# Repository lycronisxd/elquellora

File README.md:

<h3 align="center">
<picture>
  <source media="(prefers-color-scheme: dark)" srcset="images/elquellora_title_white.png">
  <source media="(prefers-color-scheme: light)" srcset="images/elquellora_title_black.png">
  
</picture><br \>
<picture>
  <source media="(prefers-color-scheme: dark)" srcset="images/author_white.png">
  <source media="(prefers-color-scheme: light)" srcset="images/author_black.png">
  
</picture>
<br \>
a lil hackpad based off the design of ulquiorra from bleach!<br \>
designed for stardance, hack club.<br \>
<br \>
<div align="center">

</div>
<hr>
<h3 align="left">get started.</h3>
<h4 align="left">
<a href="instructions.md">click here</a> to go to the instructions on how to get started!
</h4>
<hr>
<h3 align="left">about the board.</h3>
<h4 align="left">
el que llora is a 4 key hackpad with pcb art made by me,<br \>
designed with inspiration and quotes from<br \>
ulquiorra cifer from bleach!<br \>
<br \>
i wanted to make a project based off of bleach for a while<br \>
(you can probably tell by my other project <a href="https://github.com/lycronisxd/peroxide">peroxide</a>)<br \>
but finally thought of a design that would look cool in practice, so here we are!
</h4>

<hr>

<h3 align="left">features of the board.</h3>
<h4 align="left">
<ul>
<li>xiao rp2040 based</li>
<li>0.91 inch oled display</li>
<li>4x mechanical keys</li>
<li>2x ec11 rotary encoders</li>
<li>6x sk6812mini-e leds (not per-key rgb though)</li>
<li>custom bleach-inspired pcb art</li>
<li>bare-pcb design</li>
</ul>
</h4>

<hr>

<h3 align="left">design images.</h3>
<h4 align="center">
<br \>
<br \>
<br \>
<br \>
<br \>
<br \>

</h4>

<hr>

<h3 align="left">bill of materials.</h3>

|item no.|part no.|part name                 |qty.|supplier    |unit cost|total cost|notes                                            |
|--------|--------|--------------------------|----|------------|---------|----------|-------------------------------------------------|
|1       |PCB-001 |elquellora pcb            |5   |jlcpcb      | $0.40   | $7.19    |$2 for 5 pcbs + $5.12 for shipping               |
|2       |PCB-002 |seeed studio xiao rp2040  |1   |hack club   |N/A      |N/A       |provided in hackpad kit                          |
|3       |PCB-003 |1n4148 diodes             |4   |hack club   |N/A      |N/A       |provided in hackpad kit                          |
|4       |PCB-004 |0.91 inch oled            |1   |hack club   |N/A      |N/A       |provided in hackpad kit                          |
|5       |PCB-005 |ec11 rotary encoders      |2   |hack club   |N/A      |N/A       |provided in hackpad kit                          |
|6       |PCB-006 |sk6812 mini-e leds        |6   |hack club   |N/A      |N/A       |provided in hackpad kit                          |
|7       |PCB-007 |mx style switches         |4   |hack club   |N/A      |N/A       |provided in hackpad kit                          |
|8       |3D-001  |m3x5mmx4mm heatset inserts|4   |hack club   |N/A      |N/A       |provided in hackpad kit                          |
|9       |3D-002  |m3x16mm screws            |4   |hack club   |N/A      |N/A       |provided in hackpad kit                          |
|10      |3D-003  |3d printed case           |1   |print legion|?        |?         |will update when receiving a quote from a printer|
|11      |3D-004  |3d printed encoder knobs  |2   |print legion|?        |?         |will update when receiving a quote from a printer|

<hr>

<h3 align="left">my other stuff.</h3>
<h4 align="left">
a custom rp2040 dev board, <a href="https://github.com/lycronisxd/peroxide">peroxide</a><br \>
<br \>
an 18 key, per key rgb macropad with an oled screen, <a href="https://github.com/lycronisxd/pentoxide">pentoxide</a><br \>
<br \>
a custom sim-racing shifter, <a href="https://github.com/lycronisxd/a-shift">a-shift</a><br \>
<br \>
a custome corexy 3d printer, <a href="https://github.com/lycronisxd/https://github.com/lycronisxd/polylactic">polylactic</a><br \>
<br \>
a handwired split mechanical keyboard, <a href="https://github.com/lycronisxd/e-split">e-split</a>
</h4>

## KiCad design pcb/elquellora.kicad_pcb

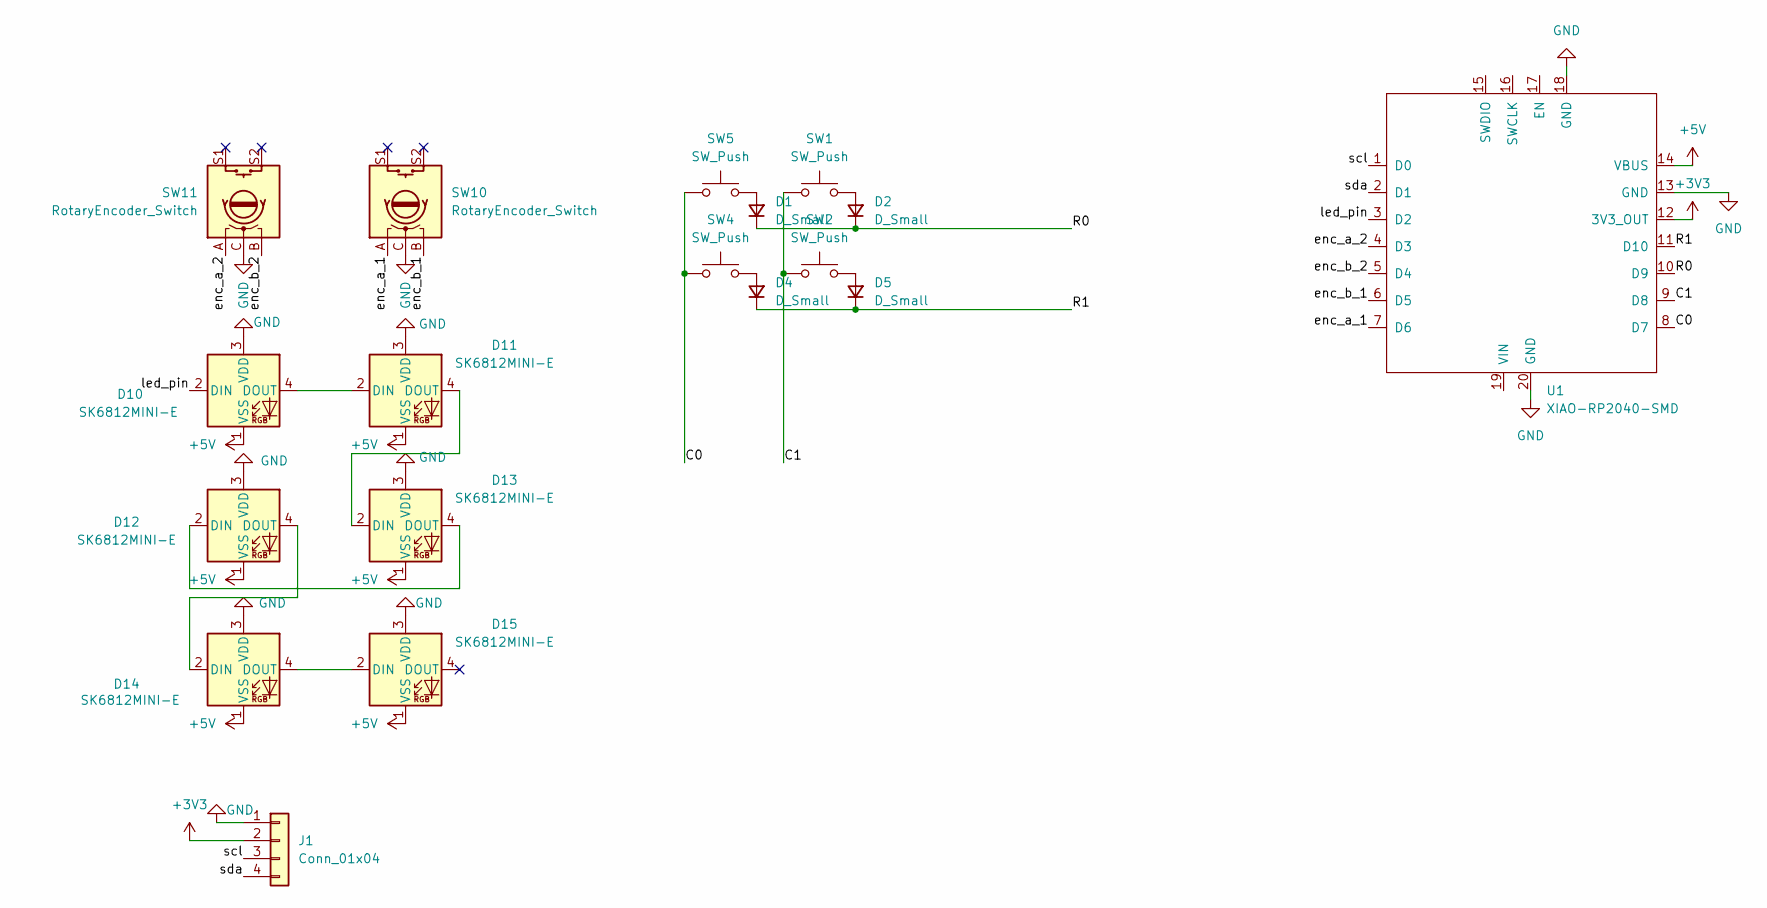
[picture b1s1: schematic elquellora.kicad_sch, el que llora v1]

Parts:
D1, D2, D4, D5: D_Small; Diode_DO-35
D10, D11, D12, D13, D14, D15: SK6812MINI-E; SK6812MINI-E_fixed
J1: Conn_01x04; PinHeader_1x04_P2.54mm_Vertical
SW1, SW2, SW4, SW5: SW_Push; SW_Cherry_MX_1.00u_PCB
SW10, SW11: RotaryEncoder_Switch; RotaryEncoder_Alps_EC11E-Switch_Vertical_H20mm
U1: XIAO-RP2040-SMD

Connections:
+3V3: J1.2, U1.12 (3V3_OUT)
+5V: D10.1 (VSS), D11.1 (VSS), D12.1 (VSS), D13.1 (VSS), D14.1 (VSS), D15.1 (VSS), U1.14 (VBUS)
/C0: SW4.1, SW5.1, U1.8 (D7)
/C1: SW1.1, SW2.1, U1.9 (D8)
/R0: D1.1 (K), D2.1 (K), U1.10 (D9)
/R1: D4.1 (K), D5.1 (K), U1.11 (D10)
/enc_a_1: SW10.A, U1.7 (D6)
/enc_a_2: SW11.A, U1.4 (D3)
/enc_b_1: SW10.B, U1.6 (D5)
/enc_b_2: SW11.B, U1.5 (D4)
/led_pin: D10.2 (DIN), U1.3 (D2)
/scl: J1.3, U1.1 (D0)
/sda: J1.4, U1.2 (D1)
GND: D10.3 (VDD), D11.3 (VDD), D12.3 (VDD), D13.3 (VDD), D14.3 (VDD), D15.3 (VDD), J1.1, SW10.C, SW11.C, U1.13 (GND), U1.18 (GND), U1.20 (GND)
unnamed: D1.2 (A), SW5.2
unnamed: D2.2 (A), SW1.2
unnamed: D4.2 (A), SW4.2
unnamed: D5.2 (A), SW2.2
unnamed: D10.4 (DOUT), D11.2 (DIN)
unnamed: D11.4 (DOUT), D13.2 (DIN)
unnamed: D12.2 (DIN), D13.4 (DOUT)
unnamed: D12.4 (DOUT), D14.2 (DIN)
unnamed: D14.4 (DOUT), D15.2 (DIN)

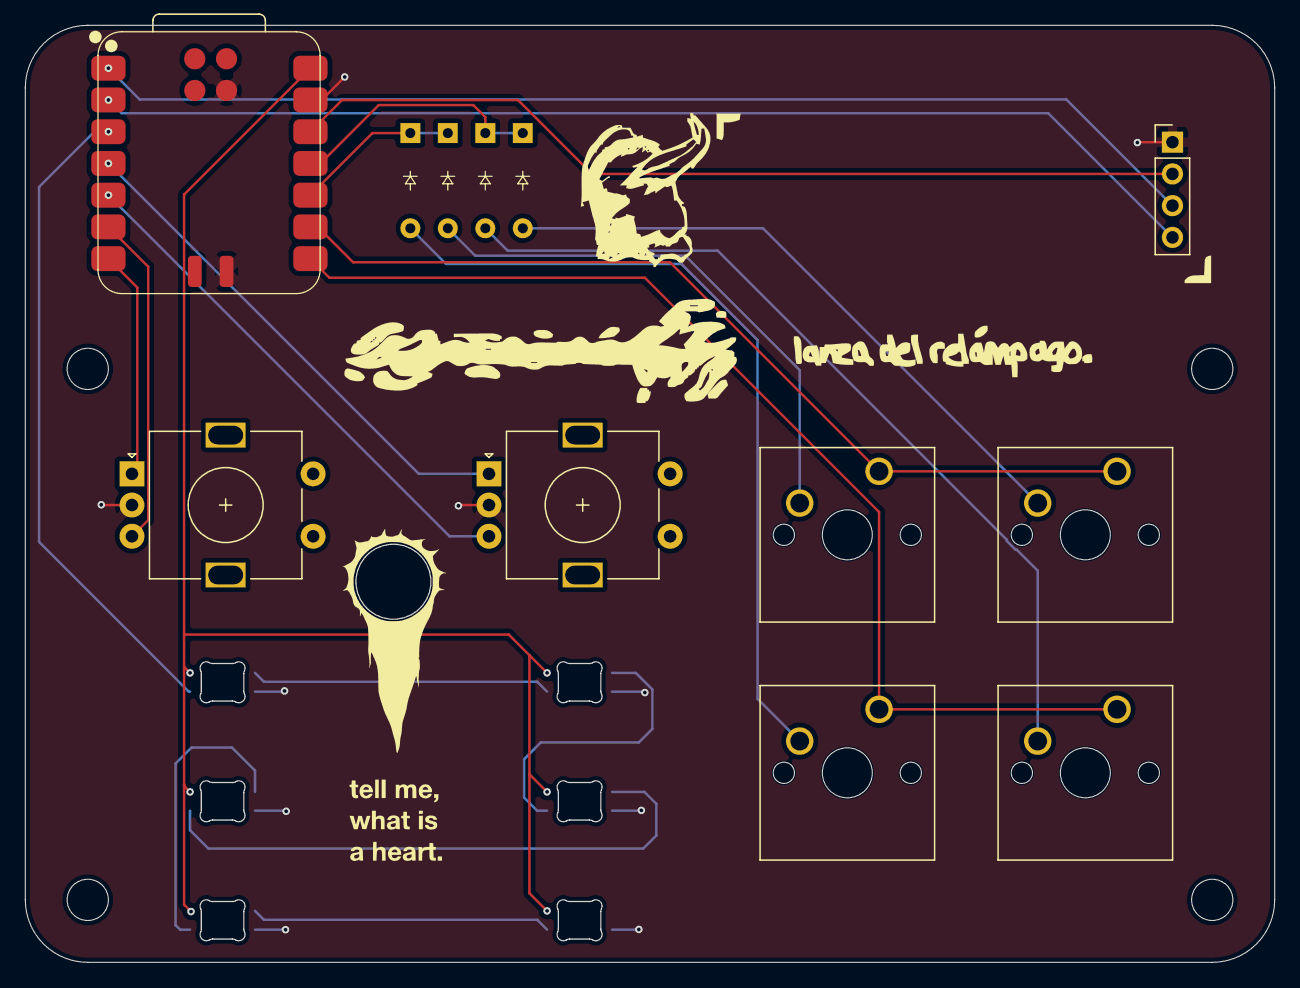
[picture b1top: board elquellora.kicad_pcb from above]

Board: 2 copper layers, 100.0 x 75.0 mm, 18 parts (0 on the bottom side), 23 nets.
